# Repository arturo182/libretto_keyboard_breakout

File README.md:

# Toshiba Libretto Keyboard Breakout

A simple board breaking out the Toshiba Libretto 20/30/50/70 keyboard.

Offers 2 possible connectors, both tested and working.

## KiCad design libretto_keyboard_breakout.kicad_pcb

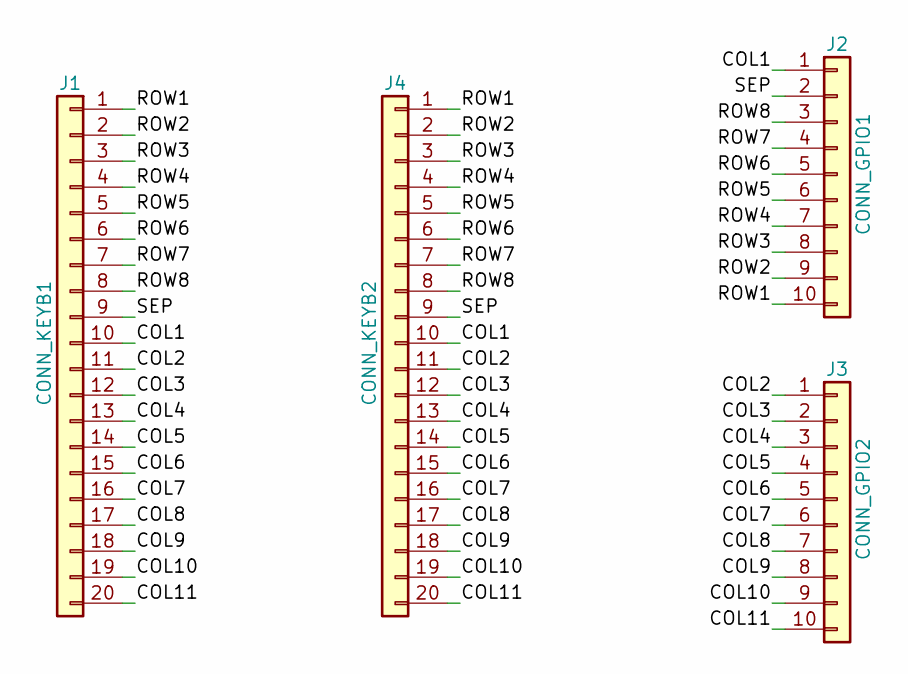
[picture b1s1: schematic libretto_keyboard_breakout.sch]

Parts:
J1: CONN_KEYB1; 2-84981-0
J2: CONN_GPIO1; PinHeader_1x10_P2.54mm_Vertical
J3: CONN_GPIO2; PinHeader_1x10_P2.54mm_Vertical
J4: CONN_KEYB2; 2-84953-0

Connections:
/COL1: J1.10, J2.1, J4.10
/COL2: J1.11, J3.1, J4.11
/COL3: J1.12, J3.2, J4.12
/COL4: J1.13, J3.3, J4.13
/COL5: J1.14, J3.4, J4.14
/COL6: J1.15, J3.5, J4.15
/COL7: J1.16, J3.6, J4.16
/COL8: J1.17, J3.7, J4.17
/COL9: J1.18, J3.8, J4.18
/COL10: J1.19, J3.9, J4.19
/COL11: J1.20, J3.10, J4.20
/ROW1: J1.1, J2.10, J4.1
/ROW2: J1.2, J2.9, J4.2
/ROW3: J1.3, J2.8, J4.3
/ROW4: J1.4, J2.7, J4.4
/ROW5: J1.5, J2.6, J4.5
/ROW6: J1.6, J2.5, J4.6
/ROW7: J1.7, J2.4, J4.7
/ROW8: J1.8, J2.3, J4.8
/SEP: J1.9, J2.2, J4.9

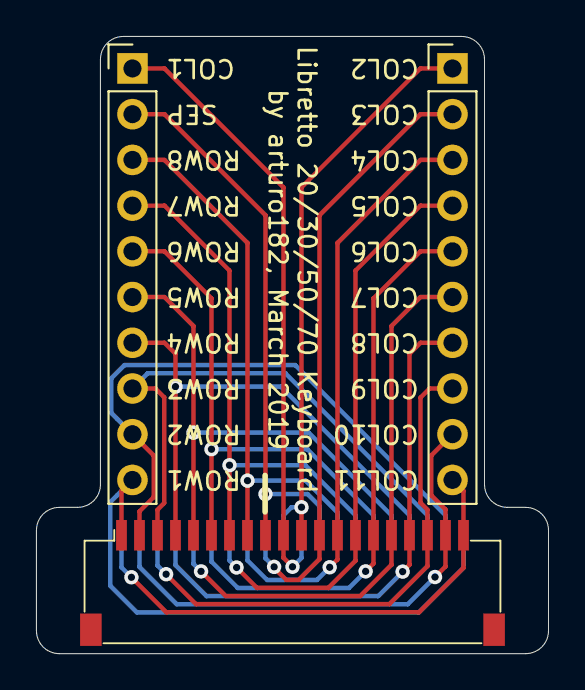
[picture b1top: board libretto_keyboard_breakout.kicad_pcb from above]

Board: 2 copper layers, 28.4 x 34.3 mm, 4 parts (1 on the bottom side), 20 nets.

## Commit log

2019-05-01 Initial import
2019-05-11 Add images
